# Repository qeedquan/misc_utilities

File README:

Simple programs for miscellaneous tasks

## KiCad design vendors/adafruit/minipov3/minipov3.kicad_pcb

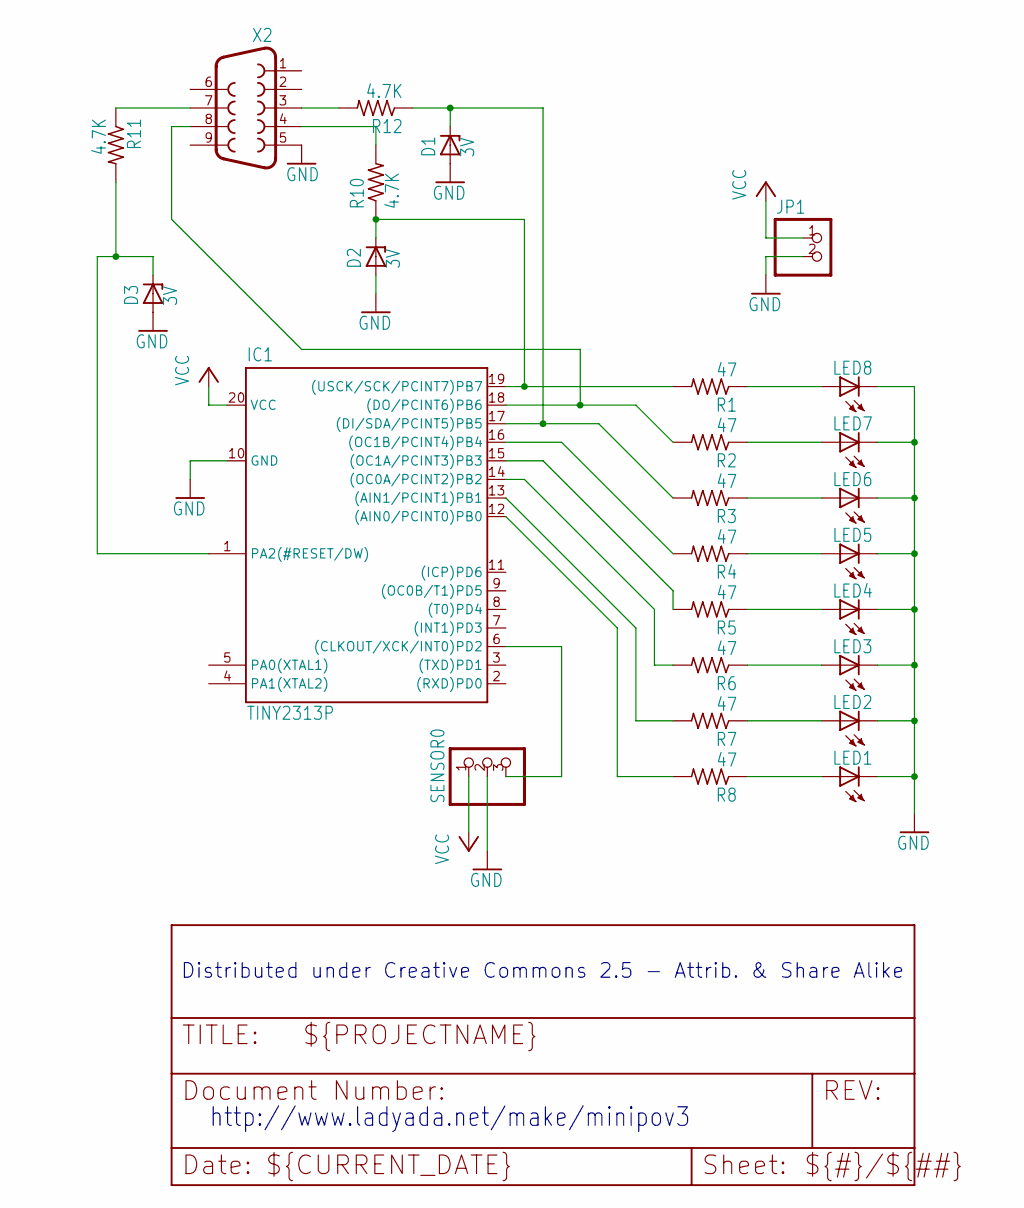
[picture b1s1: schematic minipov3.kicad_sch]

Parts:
D1, D2, D3: 3V; DO35Z10
IC1: TINY2313P; DIL20
JP1: PINHD-1X2; 1X02
LED1, LED2, LED3, LED4, LED5, LED6, LED7, LED8: LED5MM
R1, R2, R3, R4, R5, R6, R7, R8: 47; 0207_10
R10, R11, R12: 4.7K; 0207_10
SENSOR0: PINHD-1X3; 1X03
X2: F09D

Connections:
GND: D1.A, D2.A, D3.A, IC1.10 (GND), JP1.2, LED1.K (C), LED2.K (C), LED3.K (C), LED4.K (C), LED5.K (C), LED6.K (C), LED7.K (C), LED8.K (C), SENSOR0.2, X2.5
unnamed: D3.C, IC1.1 (PA2(#RESET/DW)), R11.2
unnamed: D1.C, IC1.17 ((DI/SDA/PCINT5)PB5), R3.2, R12.1
unnamed: R12.2, X2.3
unnamed: R11.1, X2.7
unnamed: R10.2, X2.4
unnamed: LED8.A, R1.1
unnamed: LED7.A, R2.1
unnamed: LED6.A, R3.1
unnamed: LED5.A, R4.1
unnamed: LED4.A, R5.1
unnamed: LED3.A, R6.1
unnamed: LED2.A, R7.1
unnamed: LED1.A, R8.1
unnamed: IC1.16 ((OC1B/PCINT4)PB4), R4.2
unnamed: IC1.15 ((OC1A/PCINT3)PB3), R5.2
unnamed: IC1.14 ((OC0A/PCINT2)PB2), R6.2
unnamed: IC1.13 ((AIN1/PCINT1)PB1), R7.2
unnamed: IC1.12 ((AIN0/PCINT0)PB0), R8.2
unnamed: IC1.6 ((CLKOUT/XCK/INT0)PD2), SENSOR0.3
unnamed: D2.C, IC1.19 ((USCK/SCK/PCINT7)PB7), R1.2, R10.1
R12: IC1.18 ((DO/PCINT6)PB6), R2.2, X2.8
VCC: IC1.20 (VCC), JP1.1, SENSOR0.1

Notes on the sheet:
http://www.ladyada.net/make/minipov3
Distributed under Creative Commons 2.5 - Attrib. & Share Alike

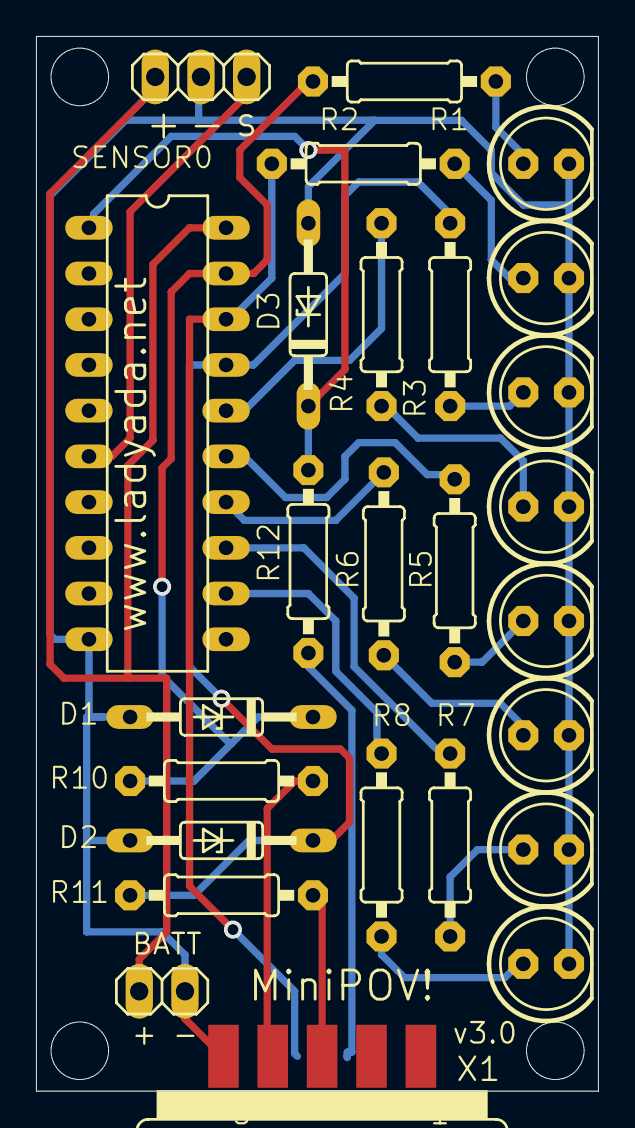
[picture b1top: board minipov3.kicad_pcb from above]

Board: 16 copper layers, 31.2 x 58.6 mm, 30 parts (0 on the bottom side), 23 nets.

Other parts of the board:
@HOLE0, @HOLE1, @HOLE2, @HOLE3: (no value)

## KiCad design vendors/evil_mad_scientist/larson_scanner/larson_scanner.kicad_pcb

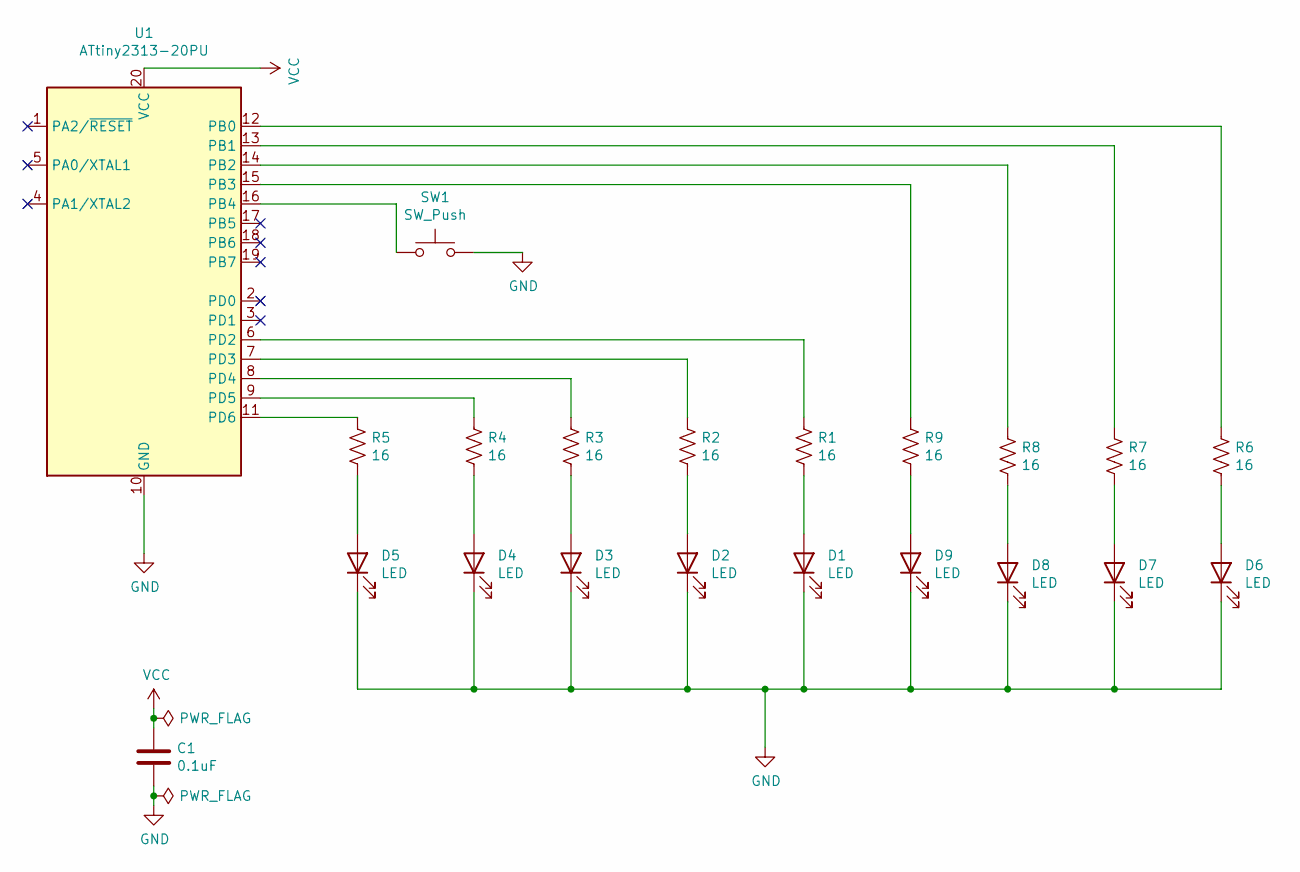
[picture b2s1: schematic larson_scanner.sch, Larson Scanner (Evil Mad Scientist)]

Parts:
C1: 0.1uF; CFR-25JR-52-16R
D1, D2, D3, D4, D5, D6, D7, D8, D9: LED; LED_D5.0mm
R1, R2, R3, R4, R5, R6, R7, R8, R9: 16; CFR-25JR-52-16R
SW1: SW_Push; CKN9102-ND
U1: ATtiny2313-20PU; DIP-20_W7.62mm

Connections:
GND: C1.2, D1.1 (K), D2.1 (K), D3.1 (K), D4.1 (K), D5.1 (K), D6.1 (K), D7.1 (K), D8.1 (K), D9.1 (K), SW1.2, U1.10 (GND)
unnamed: D1.2 (A), R1.2
unnamed: D2.2 (A), R2.2
unnamed: D3.2 (A), R3.2
unnamed: D4.2 (A), R4.2
unnamed: D5.2 (A), R5.2
unnamed: D6.2 (A), R6.2
unnamed: D7.2 (A), R7.2
unnamed: D8.2 (A), R8.2
unnamed: D9.2 (A), R9.2
unnamed: R1.1, U1.6 (PD2)
unnamed: R2.1, U1.7 (PD3)
unnamed: R3.1, U1.8 (PD4)
unnamed: R4.1, U1.9 (PD5)
unnamed: R5.1, U1.11 (PD6)
unnamed: R6.1, U1.12 (PB0)
unnamed: R7.1, U1.13 (PB1)
unnamed: R8.1, U1.14 (PB2)
unnamed: R9.1, U1.15 (PB3)
unnamed: SW1.1, U1.16 (PB4)
VCC: C1.1, U1.20 (VCC)

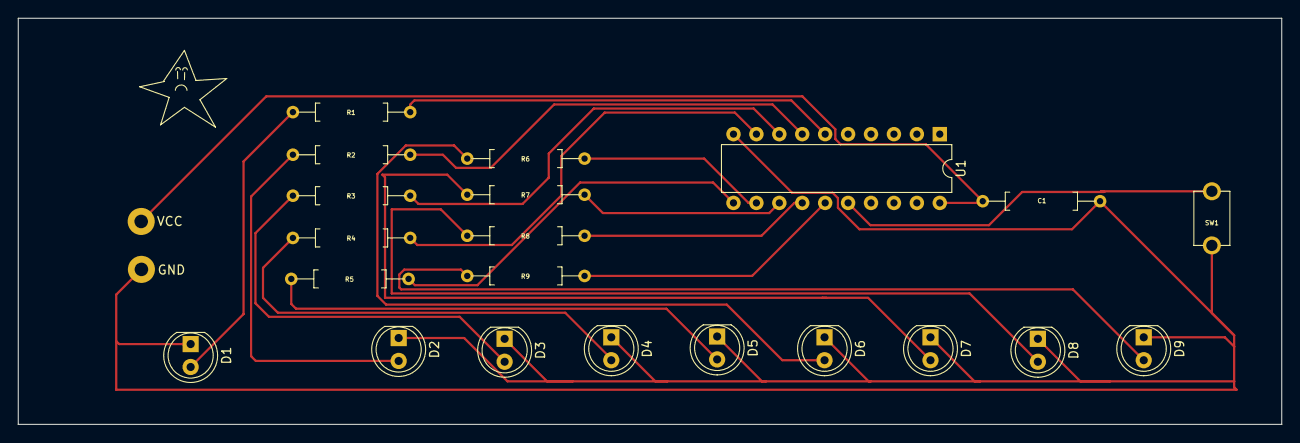
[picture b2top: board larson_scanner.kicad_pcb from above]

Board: 2 copper layers, 140.0 x 45.0 mm, 21 parts (0 on the bottom side), 21 nets.

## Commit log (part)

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2021-07-19 initial
